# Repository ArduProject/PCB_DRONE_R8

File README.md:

# Archivos de fabricación de la versión del PCB con STM32F103R8

En este repositorio encontrareis los archivos de fabricación y las listas de montaje del PCB con STM32F103**R8** que hemos visto en el curso. Enlace al curso: https://www.udemy.com/course/controlador-de-vuelo-drones-arduino-pcb/?referralCode=FD3F1CBF871EDFD84B6F

La estructura de las carpetas de este repositorio es la misma que hemos visto en el curso: una carpeta GERBER con los archivos de fabricación del PCB, y una carpeta MONTAJE con las listas de componentes y el archivo de colocación de huellas (CURSO_PCB_DRONE-all-pos.xlsx). Tambien se incluye un manual de montaje del PCB y del drone. La única diferencia con el curso es que al descargar el repositorio, dentro de la carpeta MONTAJE encontrareis dos listas en vez de una:

- Lista de componentes (BOM) para cargar en la web de JLCPCB, la lista que hemos generado en el vídeo anterior: CURSO_PCB_DRONE_BOM_JLCPCB.xlsx
- Lista con los componentes que tendremos que comprar y montar en el PCB y el drone (antena SMA, conector de batería XT60, motores, batería...): CURSO_PCB_DRONE_BOM_extra.xlsx

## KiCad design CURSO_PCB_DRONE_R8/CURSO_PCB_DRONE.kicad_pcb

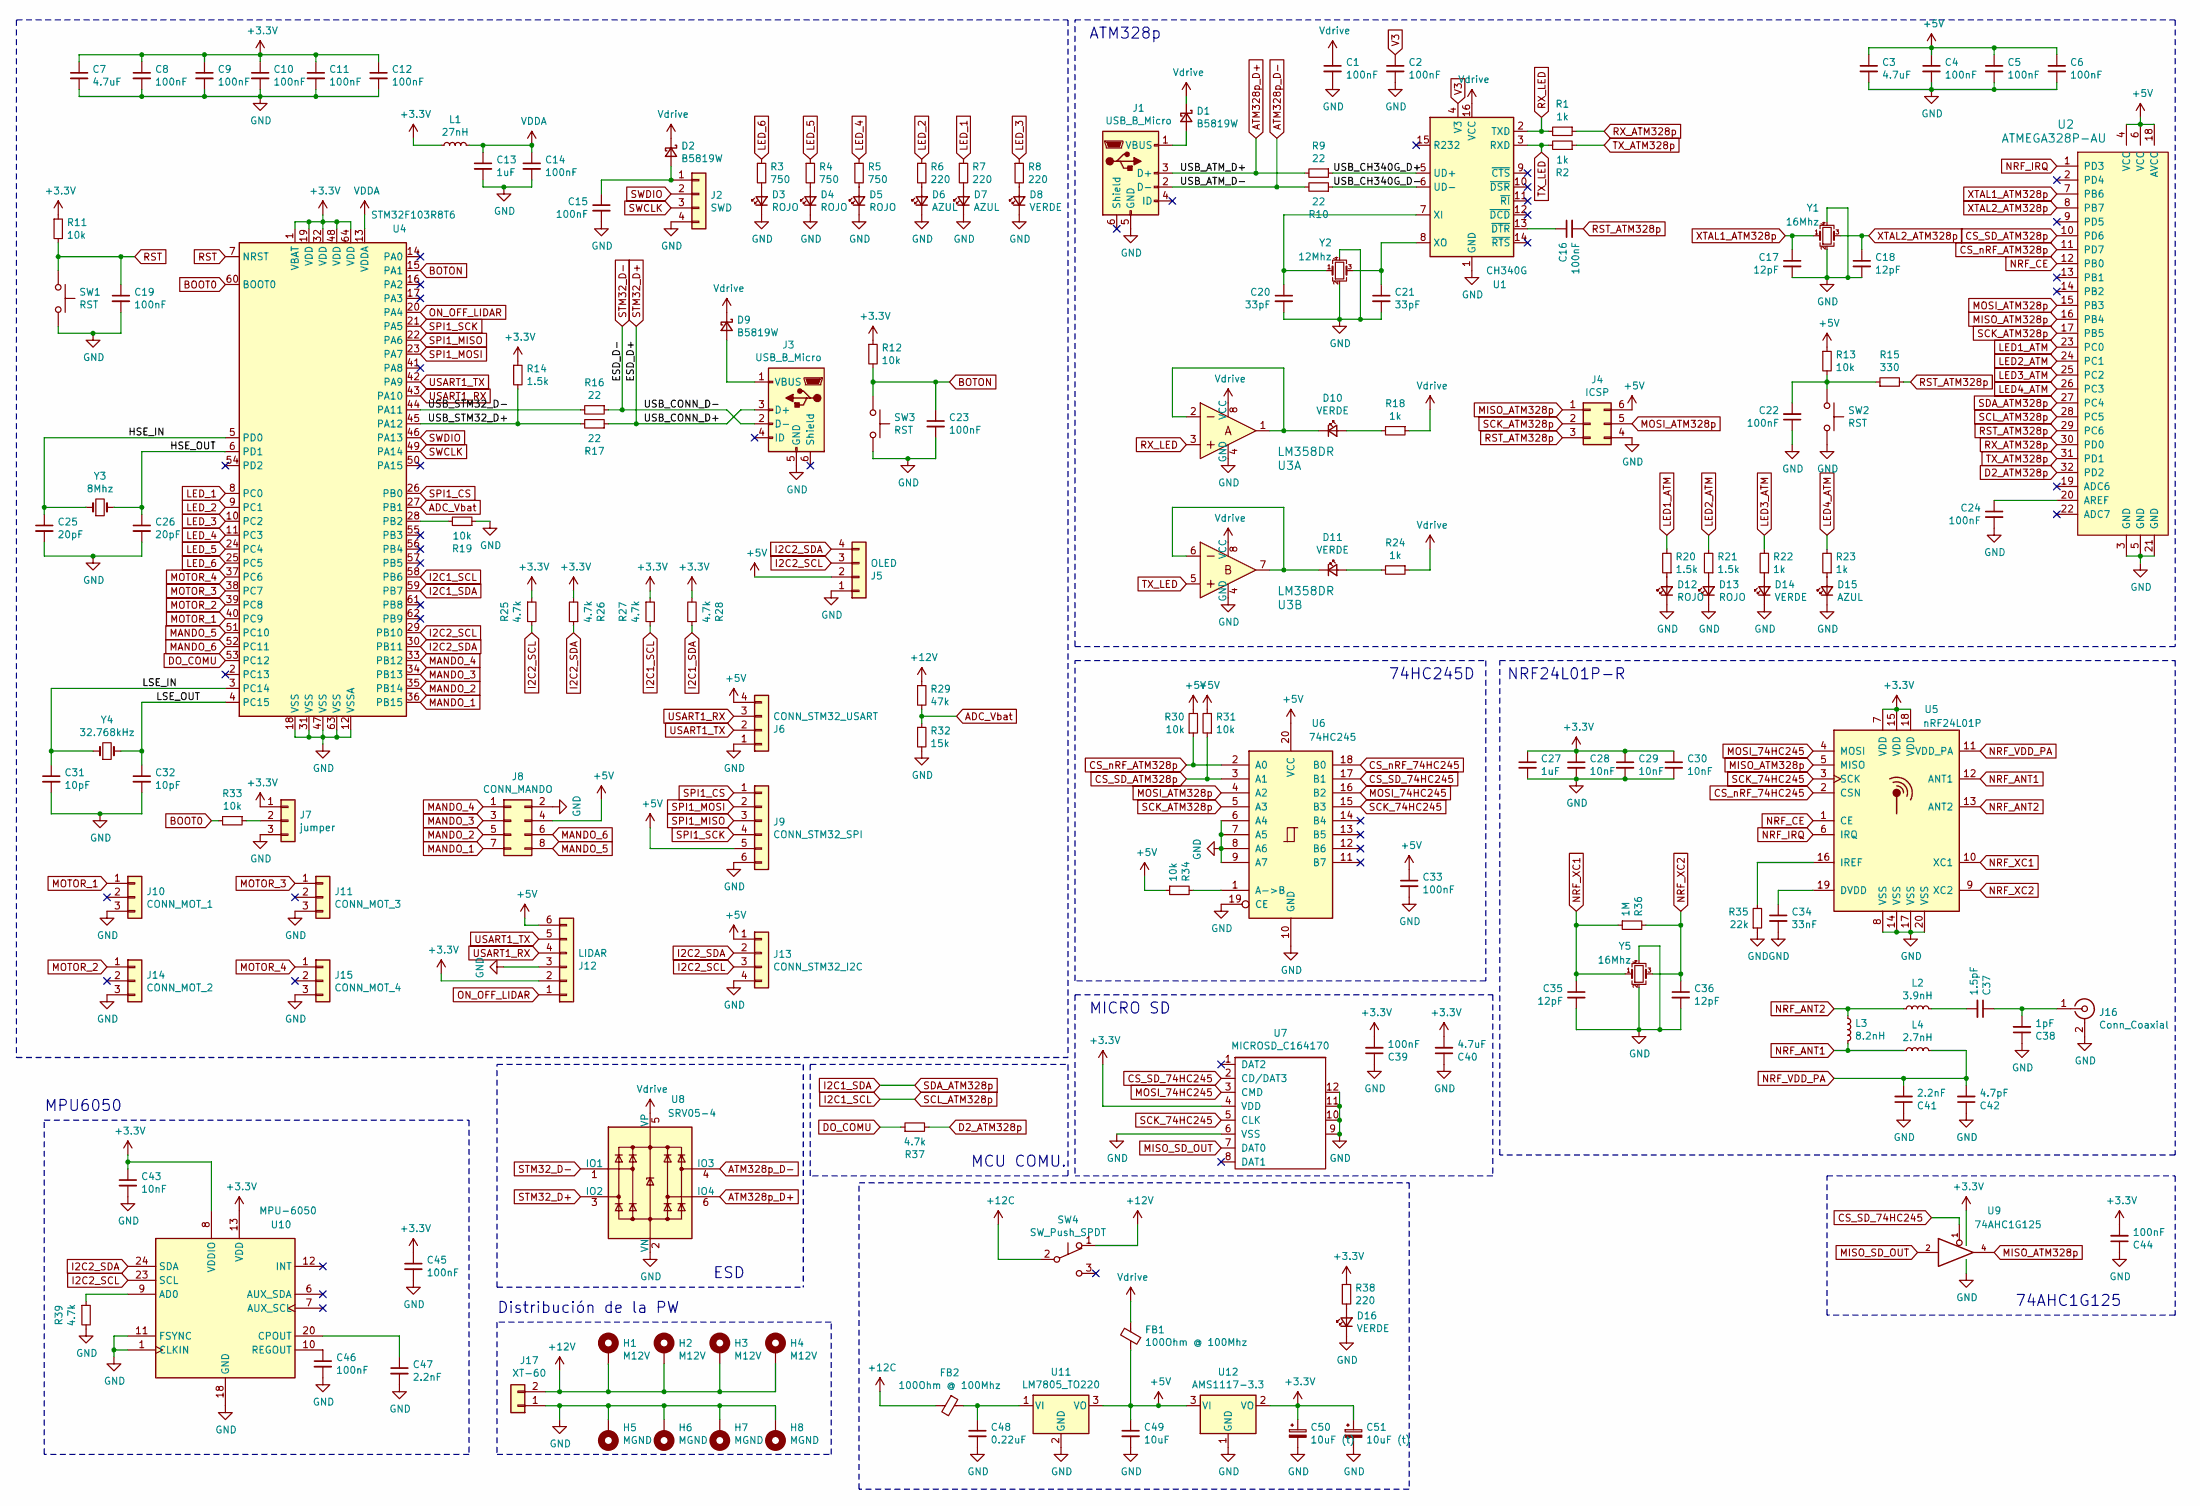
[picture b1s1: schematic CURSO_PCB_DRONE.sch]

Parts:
C1, C2, C4, C5, C6, C8, C9, C10, C11, C12, C14, C15, C16, C19, C22, C23, C24, C33, C39, C44, C45, C46: 100nF; C_0402_1005Metric
C3, C7, C40: 4.7uF; C_0402_1005Metric
C13, C27: 1uF; C_0402_1005Metric
C17, C18, C35, C36: 12pF; C_0402_1005Metric
C20, C21: 33pF; C_0402_1005Metric
C25, C26: 20pF; C_0402_1005Metric
C28, C29, C30, C43: 10nF; C_0402_1005Metric
C31, C32: 10pF; C_0402_1005Metric
C34: 33nF; C_0402_1005Metric
C37: 1.5pF; C_0402_1005Metric
C38: 1pF; C_0402_1005Metric
C41, C47: 2.2nF; C_0402_1005Metric
C42: 4.7pF; C_0402_1005Metric
C48: 0.22uF; C_1206_3216Metric
C49: 10uF; C_1206_3216Metric
C50, C51: 10uF (t); C_1206_3216Metric
D1, D2, D9: B5819W; D_SOD-123
D3, D4, D5, D12, D13: ROJO; LED_0603_1608Metric
D6, D7, D15: AZUL; LED_0603_1608Metric
D8, D10, D11, D14, D16: VERDE; LED_0603_1608Metric
FB1, FB2: 100Ohm @ 100Mhz; L_0805_2012Metric
H1, H2, H3, H4: M12V; MountingHole_3.5mm_5.5mm
H5, H6, H7, H8: MGND; MountingHole_3.5mm_5.5mm
J1, J3: USB_B_Micro; MICRO-USB-SMD_5P-P0.65-H-F_MICRO5.9MMUSB
J2: SWD; PinHeader_1x04_P2.54mm_Vertical
J4: ICSP; PinHeader_2x03_P2.54mm_Vertical
J5: OLED
J6: CONN_STM32_USART; PinHeader_1x04_P2.54mm_Horizontal
J7: jumper; PinHeader_1x03_P2.54mm_Vertical
J8: CONN_MANDO; PinHeader_2x04_P2.54mm_Vertical
J9: CONN_STM32_SPI; PinHeader_1x06_P2.54mm_Vertical
J10: CONN_MOT_1; PinHeader_1x03_P2.54mm_Vertical
J11: CONN_MOT_3; PinHeader_1x03_P2.54mm_Vertical
J12: LIDAR; PinHeader_1x06_P2.54mm_Horizontal
J13: CONN_STM32_I2C; PinHeader_1x04_P2.54mm_Vertical
J14: CONN_MOT_2; PinHeader_1x03_P2.54mm_Vertical
J15: CONN_MOT_4; PinHeader_1x03_P2.54mm_Vertical
J16: Conn_Coaxial; SMA_142-0701-201
J17: XT-60; AMASS_XT60-M
L1: 27nH; L_0402_1005Metric
L2: 3.9nH; L_0402_1005Metric
L3: 8.2nH; L_0402_1005Metric
L4: 2.7nH; L_0402_1005Metric
R1, R2: 1k; R_0402_1005Metric
R3, R4, R5: 750; R_0603_1608Metric
R6, R7, R8, R38: 220; R_0603_1608Metric
R9, R10, R16, R17: 22; R_0603_1608Metric
R11, R12, R13, R19, R30, R31, R33, R34: 10k; R_0402_1005Metric
R14: 1.5k; R_0402_1005Metric
R15: 330; R_0402_1005Metric
R18, R22, R23, R24: 1k; R_0603_1608Metric
R20, R21: 1.5k; R_0603_1608Metric
R25, R26, R27, R28, R39: 4.7k; R_0402_1005Metric
R29: 47k; R_0603_1608Metric
R32: 15k; R_0603_1608Metric
R35: 22k; R_0402_1005Metric
R36: 1M; R_0402_1005Metric
R37: 4.7k; R_0603_1608Metric
SW1, SW2, SW3: RST; KEY-TH_2P-L6.0-W3.5-P6.50
SW4: SW_Push_SPDT; Switch_Slide
U1: CH340G; SOIC-16_3.9x9.9mm_P1.27mm
U2: ATMEGA328P-AU; TQFP-32_7x7mm; MPN ATMEGA328P-AU; Digi-Key_PN ATMEGA328P-AU-ND
U3: LM358DR; SOIC-8_W3.9mm; MPN LM358DR; Digi-Key_PN 296-1014-1-ND
U4: STM32F103R8T6; LQFP-64_10x10mm_P0.5mm
U5: nRF24L01P; QFN-20-1EP_4x4mm_P0.5mm_EP2.5x2.5mm
U6: 74HC245; SOIC-20W_7.5x12.8mm_P1.27mm
U7: MICROSD_C164170; TF-SMD_472192001
U8: SRV05-4; SOT-23-6
U9: 74AHC1G125; SOT-353_SC-70-5
U10: MPU-6050; InvenSense_QFN-24_4x4mm_P0.5mm
U11: LM7805_TO220; TO-220-3_Horizontal_TabDown
U12: AMS1117-3.3; SOT-223-3_TabPin2
Y1, Y5: 16Mhz; Crystal_SMD_3225-4Pin_3.2x2.5mm
Y2: 12Mhz; Crystal_SMD_3225-4Pin_3.2x2.5mm
Y3: 8Mhz; Crystal_SMD_5032-2Pin_5.0x3.2mm
Y4: 32.768kHz; Crystal_SMD_2012-2Pin_2.0x1.2mm

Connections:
+3V3: C7.1, C8.1, C9.1, C10.1, C11.1, C12.1, C27.1, C28.1, C29.1, C30.1, C39.2, C40.2, C43.1, C44.2, C45.1, C50.1, C51.1, J7.1, J12.2, L1.1, R11.1, R12.1, R14.1, R25.1, R26.2, R27.1, R28.2, R38.1, U4.1 (VBAT), U4.19 (VDD), U4.32 (VDD), U4.48 (VDD), U4.64 (VDD), U5.7 (VDD), U5.15 (VDD), U5.18 (VDD), U7.4 (VDD), U9.5 (VCC), U10.8 (VDDIO), U10.13 (VDD), U12.2 (VO)
+5V: C3.1, C4.1, C5.1, C6.1, C33.1, C49.1, FB1.1, J4.6, J5.2, J6.4, J8.4, J9.5, J12.6, J13.1, R13.1, R30.2, R31.2, R34.1, U2.4 (VCC), U2.6 (VCC), U2.18 (AVCC), U6.20 (VCC), U11.3 (VO), U12.3 (VI)
+12C: FB2.2, SW4.2 (B)
+12V: H1.1, H2.1, H3.1, H4.1, J17.2, R29.1, SW4.1 (A)
/HSE_IN: C25.1, U4.5 (PD0), Y3.1
/HSE_OUT: C26.1, U4.6 (PD1), Y3.2
/LSE_IN: C31.1, U4.3 (PC14), Y4.1
/LSE_OUT: C32.1, U4.4 (PC15), Y4.2
/USB_CH340G_D+: R9.1, U1.5 (UD+)
/USB_CH340G_D-: R10.1, U1.6 (UD-)
/USB_STM32_D+: R14.2, R17.2, U4.45 (PA12)
/USB_STM32_D-: R16.2, U4.44 (PA11)
ADC_Vbat: R29.2, R32.1, U4.27 (PB1)
ATM328p_D+: J1.3 (D+), R9.2, U8.6 (IO4)
ATM328p_D-: J1.2 (D-), R10.2, U8.4 (IO3)
BOOT0: R33.2, U4.60 (BOOT0)
BOTON: C23.1, R12.2, SW3.1, U4.15 (PA1)
CS_SD_74HC245: U6.17 (B1), U7.2 (CD/DAT3), U9.1
CS_SD_ATM328p: R31.1, U2.10 (PD6), U6.3 (A1)
CS_nRF_74HC245: U5.2 (CSN), U6.18 (B0)
CS_nRF_ATM328p: R30.1, U2.11 (PD7), U6.2 (A0)
D2_ATM328p: R37.2, U2.32 (PD2)
DO_COMU: R37.1, U4.53 (PC12)
GND: C1.2, C2.2, C3.2, C4.2, C5.2, C6.2, C7.2, C8.2, C9.2, C10.2, C11.2, C12.2, C13.2, C14.2, C15.2, C17.2, C18.2, C19.2, C20.2, C21.2, C22.1, C23.2, C24.2, C25.2, C26.2, C27.2, C28.2, C29.2, C30.2, C31.2, C32.2, C33.2, C34.2, C35.2, C36.2, C38.1, C39.1, C40.1, C41.1, C42.1, C43.2, C44.1, C45.2, C46.2, C47.2, C48.2, C49.2, C50.2, C51.2, D3.1 (K), D4.1 (K), D5.1 (K), D6.1 (K), D7.1 (K), D8.1 (K), D12.1 (K), D13.1 (K), D14.1 (K), D15.1 (K), D16.1 (K), H5.1, H6.1, H7.1, H8.1, J1.5 (GND), J2.4, J3.5 (GND), J4.4, J5.1, J6.1, J7.3, J8.2, J9.6, J10.3, J11.3, J12.3, J13.4, J14.3, J15.3, J16.2 (Ext), J17.1, R19.1, R32.2, R35.1, R39.2, SW1.2, SW2.2, SW3.2, U1.1 (GND), U2.3 (GND), U2.5 (GND), U2.21 (GND), U3.4 (GND), U4.12 (VSSA), U4.18 (VSS), U4.31 (VSS), U4.47 (VSS), U4.63 (VSS), U5.8 (VSS), U5.14 (VSS), U5.17 (VSS), U5.20 (VSS), U6.6 (A4), U6.7 (A5), U6.8 (A6), U6.9 (A7), U6.10 (GND), U6.19 (CE), U7.6 (VSS), U7.9, U7.10, U7.11, U7.12, U8.2 (VN), U9.3 (GND), U10.1 (CLKIN), U10.11 (FSYNC), U10.18 (GND), U11.2 (GND), U12.1 (GND), Y1.2, Y1.4, Y2.2, Y2.4, Y5.2, Y5.4
I2C1_SCL: R27.2, U2.28 (PC5), U4.58 (PB6)
I2C1_SDA: R28.1, U2.27 (PC4), U4.59 (PB7)
I2C2_SCL: J5.3, J13.3, R25.2, U4.29 (PB10), U10.23 (SCL)
I2C2_SDA: J5.4, J13.2, R26.1, U4.30 (PB11), U10.24 (SDA)
LED1_ATM: R20.2, U2.23 (PC0)
LED2_ATM: R21.2, U2.24 (PC1)
LED3_ATM: R22.2, U2.25 (PC2)
LED4_ATM: R23.2, U2.26 (PC3)
LED_1: R7.1, U4.8 (PC0)
LED_2: R6.1, U4.9 (PC1)
LED_3: R8.1, U4.10 (PC2)
LED_4: R5.1, U4.11 (PC3)
LED_5: R4.1, U4.24 (PC4)
LED_6: R3.1, U4.25 (PC5)
MANDO_1: J8.7, U4.36 (PB15)
MANDO_2: J8.5, U4.35 (PB14)
MANDO_3: J8.3, U4.34 (PB13)
MANDO_4: J8.1, U4.33 (PB12)
MANDO_5: J8.8, U4.51 (PC10)
MANDO_6: J8.6, U4.52 (PC11)
MISO_ATM328p: J4.1, U2.16 (PB4), U5.5 (MISO), U9.4
MISO_SD_OUT: U7.7 (DAT0), U9.2
MOSI_74HC245: U5.4 (MOSI), U6.16 (B2), U7.3 (CMD)
MOSI_ATM328p: J4.5, U2.15 (PB3), U6.4 (A2)
MOTOR_1: J10.1, U4.40 (PC9)
MOTOR_2: J14.1, U4.39 (PC8)
MOTOR_3: J11.1, U4.38 (PC7)
MOTOR_4: J15.1, U4.37 (PC6)
NRF_ANT1: L3.2, L4.1, U5.12 (ANT1)
NRF_ANT2: L2.1, L3.1, U5.13 (ANT2)
NRF_CE: U2.12 (PB0), U5.1 (CE)
NRF_IRQ: U2.1 (PD3), U5.6 (IRQ)
NRF_VDD_PA: C41.2, C42.2, L4.2, U5.11 (VDD_PA)
NRF_XC1: C35.1, R36.1, U5.10 (XC1), Y5.1
NRF_XC2: C36.1, R36.2, U5.9 (XC2), Y5.3
unnamed: C15.1, D2.2 (A), J2.1
unnamed: C16.1, U1.13 (~DTR)
unnamed: C20.1, U1.7 (XI), Y2.1
unnamed: C21.1, U1.8 (XO), Y2.3
unnamed: C22.2, R13.2, R15.1, SW2.1
unnamed: C24.1, U2.20 (AREF)
unnamed: C34.1, U5.19 (DVDD)
unnamed: C37.1, C38.2, J16.1 (In)
unnamed: C37.2, L2.2
unnamed: C46.1, U10.10 (REGOUT)
unnamed: C47.1, U10.20 (CPOUT)
unnamed: C48.1, FB2.1, U11.1 (VI)
unnamed: D1.2 (A), J1.1 (VBUS)
unnamed: D3.2 (A), R3.2
unnamed: D4.2 (A), R4.2
unnamed: D5.2 (A), R5.2
unnamed: D6.2 (A), R6.2
unnamed: D7.2 (A), R7.2
unnamed: D8.2 (A), R8.2
unnamed: D9.2 (A), J3.1 (VBUS)
unnamed: D10.1 (K), U3.1, U3.2
unnamed: D10.2 (A), R18.2
unnamed: D11.1 (K), U3.6, U3.7
unnamed: D11.2 (A), R24.2
unnamed: D12.2 (A), R20.1
unnamed: D13.2 (A), R21.1
unnamed: D14.2 (A), R22.1
unnamed: D15.2 (A), R23.1
unnamed: D16.2 (A), R38.2
unnamed: J7.2, R33.1
unnamed: R19.2, U4.28 (PB2)
unnamed: R34.2, U6.1 (A->B)
unnamed: R35.2, U5.16 (IREF)
unnamed: R39.1, U10.9 (AD0)
ON_OFF_LIDAR: J12.1, U4.20 (PA4)
RST: C19.1, R11.2, SW1.1, U4.7 (NRST)
RST_ATM328p: C16.2, J4.3, R15.2, U2.29 (PC6)
RX_ATM328p: R1.1, U2.30 (PD0)
RX_LED: R1.2, U1.2 (TXD), U3.3
SCK_74HC245: U5.3 (SCK), U6.15 (B3), U7.5 (CLK)
SCK_ATM328p: J4.2, U2.17 (PB5), U6.5 (A3)
SPI1_CS: J9.1, U4.26 (PB0)
SPI1_MISO: J9.3, U4.22 (PA6)
SPI1_MOSI: J9.2, U4.23 (PA7)
SPI1_SCK: J9.4, U4.21 (PA5)
STM32_D+: J3.3 (D+), R17.1, U8.3 (IO2)
STM32_D-: J3.2 (D-), R16.1, U8.1 (IO1)
SWCLK: J2.3, U4.49 (PA14)
SWDIO: J2.2, U4.46 (PA13)
TX_ATM328p: R2.1, U2.31 (PD1)
TX_LED: R2.2, U1.3 (RXD), U3.5
USART1_RX: J6.3, J12.4, U4.43 (PA10)
USART1_TX: J6.2, J12.5, U4.42 (PA9)
V3: C2.1, U1.4 (V3)
VDDA: C13.1, C14.1, L1.2, U4.13 (VDDA)
Vdrive: C1.1, D1.1 (K), D2.1 (K), D9.1 (K), FB1.2, R18.1, R24.1, U1.16 (VCC), U3.8 (VCC), U8.5 (VP)
XTAL1_ATM328p: C17.1, U2.7 (PB6), Y1.1
XTAL2_ATM328p: C18.1, U2.8 (PB7), Y1.3

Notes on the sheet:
ESD
MPU6050
Distribución de la PW
MCU COMU.
MICRO SD
NRF24L01P-R
74HC245D
ATM328p
74AHC1G125

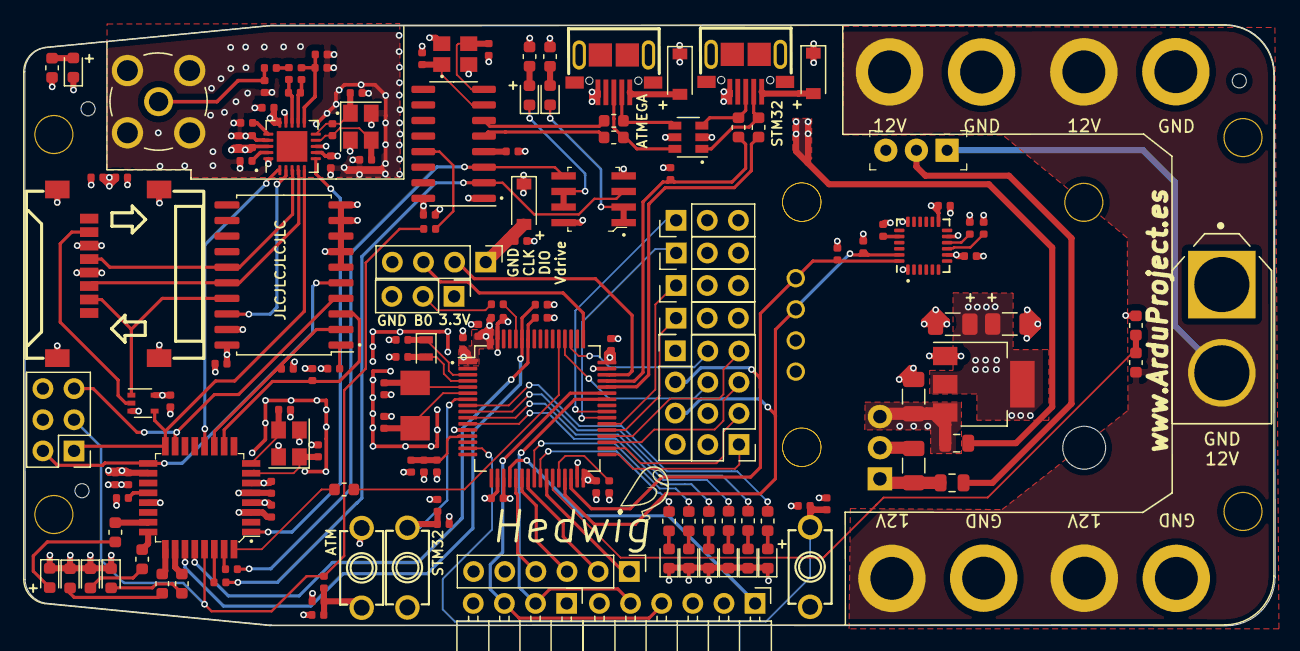
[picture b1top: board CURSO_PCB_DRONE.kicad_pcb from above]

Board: 4 copper layers, 102.0 x 49.0 mm, 158 parts (1 on the bottom side), 117 nets.

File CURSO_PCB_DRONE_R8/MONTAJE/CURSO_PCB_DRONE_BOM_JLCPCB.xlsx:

Designator | Footprint | Comment | JLCPCB Part #
Y3 | Crystal_SMD_5032-2Pin_5.0x3.2mm | 8Mhz | C115962
J3,J1 | MICRO-USB-SMD_5P-P0.65-H-F_MICRO5.9MMUSB | USB_B_Micro | C393940
Y2 | Crystal_SMD_3225-4Pin_3.2x2.5mm | 12Mhz | C9002
U7 | TF-SMD_472192001 | MICROSD_C164170 | C164170
U10 | InvenSense_QFN-24_4x4mm_P0.5mm | MPU-6050 | C24112
C43,C28,C29,C30 | C_0402_1005Metric | 10nF | C15195
U4 | LQFP-64_10x10mm_P0.5mm | STM32F103R8T6 | C46034
U1 | SOIC-16_3.9x9.9mm_P1.27mm | CH340G | C14267
C1,C2,C4,C5,C6,C10,C11,C12,C14,C15,C16,C19,C22,C23,C24,C33,C39,C44,C45,C46,C8,C9 | C_0402_1005Metric | 100nF | C1525
C3,C7,C40 | C_0402_1005Metric | 4.7uF | C23733
C13,C27 | C_0402_1005Metric | 1uF | C52923
C17,C18,C35,C36 | C_0402_1005Metric | 12pF | C1547
C20,C21 | C_0402_1005Metric | 33pF | C1562
C25,C26 | C_0402_1005Metric | 20pF | C1554
C31,C32 | C_0402_1005Metric | 10pF | C32949
C34 | C_0402_1005Metric | 33nF | C1585
C37 | C_0402_1005Metric | 1.5pF | C1552
C38 | C_0402_1005Metric | 1pF | C1550
C41,C47 | C_0402_1005Metric | 2.2nF | C1531
C42 | C_0402_1005Metric | 4.7pF | C1569
C48 | C_1206_3216Metric | 0.22uF | C1857
C49 | C_1206_3216Metric | 10uF | C13585
C50,C51 | C_1206_3216Metric | 10uF (t) | C7171
D3,D4,D5,D12,D13 | LED_0603_1608Metric | ROJO | C2286
D6,D7,D15 | LED_0603_1608Metric | AZUL | C72041
D8,D10,D11,D14,D16 | LED_0603_1608Metric | VERDE | C72043
FB1,FB2 | L_0805_2012Metric | 100Ohm @ 100Mhz | C1015
L1 | L_0402_1005Metric | 27nH | C18830
L2 | L_0402_1005Metric | 3.9nH | C14033
L3 | L_0402_1005Metric | 8.2nH | C16208
L4 | L_0402_1005Metric | 2.7nH | C27123
R1,R2 | R_0402_1005Metric | 1k | C11702
R11,R12,R13,R30,R31,R33,R34,R19 | R_0402_1005Metric | 10k | C25744
R14 | R_0402_1005Metric | 1.5k | C25867
R15 | R_0402_1005Metric | 330 | C25104
R20,R21 | R_0603_1608Metric | 1.5k | C22843
R22,R23,R24,R18 | R_0603_1608Metric | 1k | C21190
R25,R26,R27,R28,R39 | R_0402_1005Metric | 4.7k | C25900
R35 | R_0402_1005Metric | 22k | C25768
R36 | R_0402_1005Metric | 1M | C26083
SW1,SW2,SW3 | KEY-TH_2P-L6.0-W3.5-P6.50 | RST | C221867
U2 | TQFP-32_7x7mm | ATMEGA328P-AU | C14877
U3 | SOIC-8_W3.9mm | LM358DR | C7950
U5 | QFN-20-1EP_4x4mm_P0.5mm_EP2.5x2.5mm | nRF24L01P | C8791
U6 | SOIC-20W_7.5x12.8mm_P1.27mm | 74HC245 | C5625
U8 | SOT-23-6 | SRV05-4 | C85364
U9 | SOT-353_SC-70-5 | 74AHC1G125 | C151890
U12 | SOT-223-3_TabPin2 | AMS1117-3.3 | C6186
Y1,Y5 | Crystal_SMD_3225-4Pin_3.2x2.5mm | 16Mhz | C13738
Y4 | Crystal_SMD_2012-2Pin_2.0x1.2mm | 32.768kHz | C97602
R9,R10,R16,R17 | R_0603_1608Metric | 22 | C23345
R37 | R_0603_1608Metric | 4.7k | C23162
R3,R4,R5 | R_0603_1608Metric | 750 | C23241
R6,R7,R8,R38 | R_0603_1608Metric | 220 | C22962
R29 | R_0603_1608Metric | 47k | C25819
R32 | R_0603_1608Metric | 15k | C22809
D1,D2,D9 | D_SOD-123 | B5819W | C8598

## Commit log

2022-01-09 Add files via upload
    Se añade manual de montaje del PCB y del drone
2022-01-10 Add files via upload
    Se completa el documento de montaje del PCB y del drone con enlace al software de validación básica
2022-01-13 Add files via upload
    Se completa el manual de montaje
2024-01-12 Add files via upload
    Había un error y las pistas que alimentaban el PCB desde los conectaos USB no estaban tiradas.
